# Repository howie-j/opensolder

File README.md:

# OpenSolder
  
Fully open source JBC T245-compatible soldering station and iron holder

## Introduction
When my cheap T12 clone soldering station went up in smoke, i started looking into either buying a JBC CDB, or building a proper soldering station. The internet is already crowded with DIY JBC compatible stations, but most are poorly documented, or does not have the quality-of-life features that the original have.

The [unisolder project](https://github.com/sparkybg/UniSolder-5.2) is absolutely impressive, but waaay to complex and "universal" for my needs. [Marco Reps](https://youtu.be/GYIiOkr6x9o) built a cool C470 station, and i liked the simplicity of that.

## Goals:
- _T12 clone like_ form factor station that does not take up valuable bench space
- JBC T245 tip compatibility, with similar performance to the original station
- QoL features that the CDB station have, like auto standby, tip remover, holder, tip cleaner ect.
- Simple design using cheap off-the-shelf parts
- A compact handle stand with these features:
	- Detection when the handle is in the tool holder (auto standby)
	- Detection when you're about to swap tips (cut power)
	- Integrated tip remover, tip storage, tip cleaner and a soldering wire spool holder
	- Simple to build

## Design Specifications
- 24V toroidal transformer
- Zero Crossing AC switching
- OLED display and rotary encoder for adjusting temperature
- Compact and low profile design
- Super fast heatup time
- Hardware should be mostly 3D printable, and easy to build using regular tools

## Station
  
The station is built in a Hammond enclosure, with a center mounted transformer. The PCB is mounted to the custom front panel, and all 230VAC connections is in the rear of the chassis.
There is two connectors on the rear panel, one for connecting to the stand, and an optional ST-link connector for firmware upgrades.

## Stand
  
The stand consists of 3D-printed parts, a genuine JBC tool holder, a tip remover made from aluminium angle and some hardware. 

## Schematic

## PCB

The PCB is fairly low density, uses 0805 SMD components and is fully hand solderable with a microscope.

[Check out the awesome interactive BOM!](http://htmlpreview.github.io/?https://github.com/howie-j/OpenSolder/blob/main/Electronics/BOM/Interactive_BOM.html)

## Firmware
Coming soon... :)

## Links and Sources

[The unisolder project](https://github.com/sparkybg/UniSolder-5.2)  
[Marco Reps](https://youtu.be/GYIiOkr6x9o)  
[foldvarid93's JBC Soldering Station](https://github.com/foldvarid93/JBC_SolderingStation)  
[johnmx's eevblog thread](https://eevblog.com/forum/testgear/jbc-soldering-station-cd-2bc-complete-schematic-analysis/)

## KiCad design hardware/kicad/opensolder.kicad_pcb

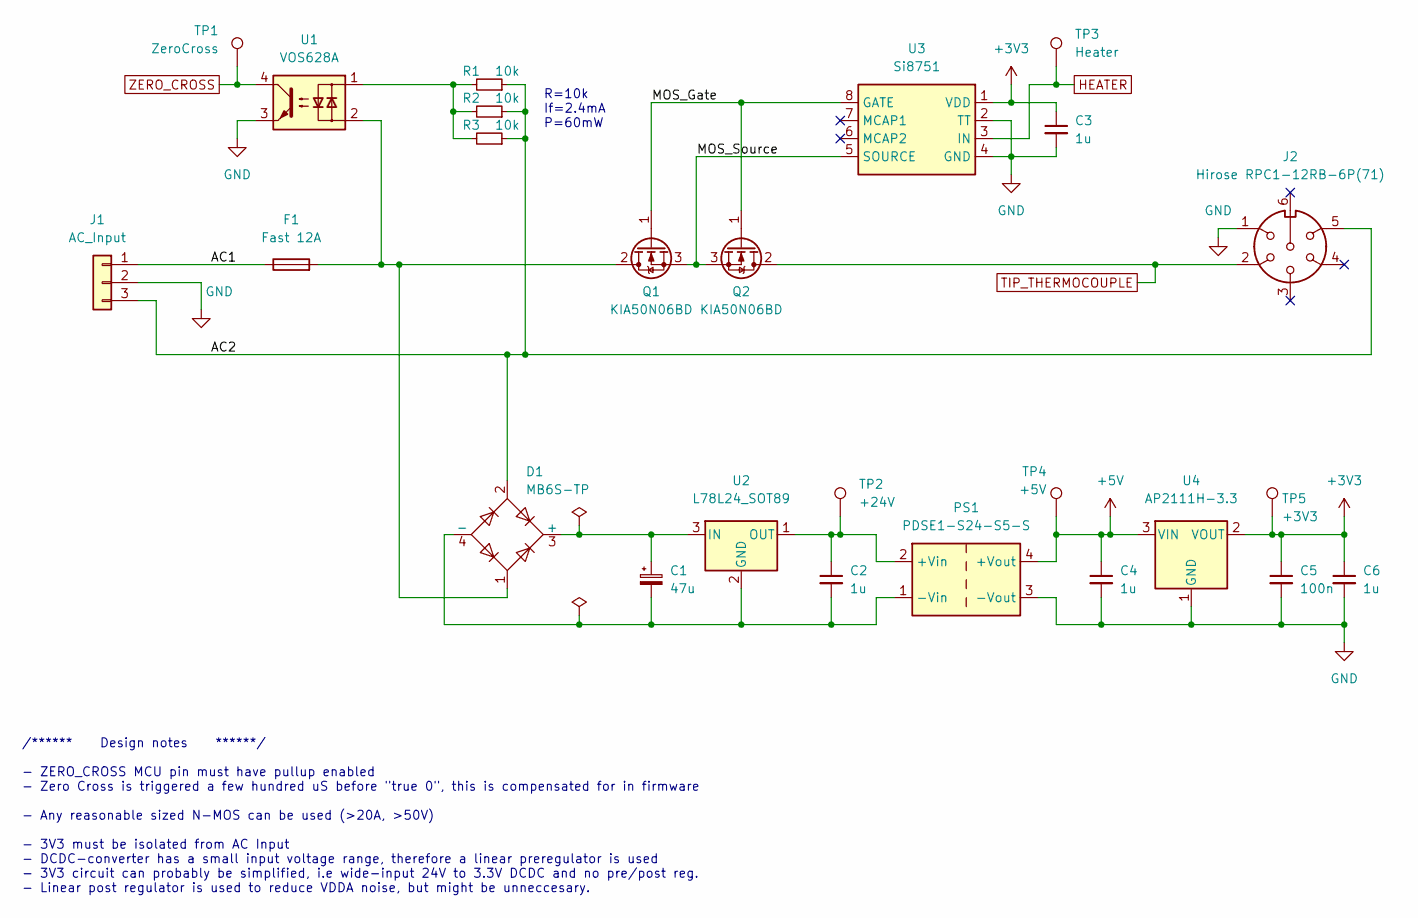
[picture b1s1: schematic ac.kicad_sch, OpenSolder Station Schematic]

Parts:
C1: 47u; CP_Radial_D8.0mm_P3.50mm
C2, C3, C4, C6: 1u; C_1210_3225Metric
C5: 100n; C_0805_2012Metric
D1: MB6S-TP; TO-269AA
F1: Fast 12A; Fuseholder_Cylinder-5x20mm_Schurter_0031_8201_Horizontal_Op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
J1: AC_Input; PhoenixContact_MSTBVA_2,5_3-G_1x03_P5.00mm_Vertical
J2: Hirose RPC1-12RB-6P(71); Hirose_RPC1
PS1: PDSE1-S24-S5-S; PDSE1_DCDC
Q1, Q2: KIA50N06BD; TO-252-2
R1, R2, R3: 10k; R_0805_2012Metric
TP1: ZeroCross; TestPoint_Pad_D1.0mm
TP2: +24V; TestPoint_Pad_D1.0mm
TP3: Heater; TestPoint_Pad_D1.0mm
TP4: +5V; TestPoint_Pad_D1.0mm
TP5: +3V3; TestPoint_Pad_D1.0mm
U1: VOS628A; SOP-4_4.4x2.6mm_P1.27mm
U2: L78L24_SOT89; SOT-89-3
U3: Si8751; SOIC-8_3.9x4.9mm_P1.27mm
U4: AP2111H-3.3; SOT-223

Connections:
+3V3: C3.1, C5.1, C6.1, TP5.1, U3.1 (VDD), U4.2 (VOUT); also elsewhere on the board
+5V: C4.1, PS1.4 (+Vout), TP4.1, U4.3 (VIN)
/AC/AC1: F1.1, J1.1
/AC/AC2: D1.2, J1.3, J2.5, R1.1, R2.1, R3.1
/AC/MOS_Gate: Q1.1 (G), Q2.1 (G), U3.8 (GATE)
/AC/MOS_Source: Q1.3 (S), Q2.3 (S), U3.5 (SOURCE)
GND: C3.2, C4.2, C5.2, C6.2, J1.2, J2.1, PS1.3 (-Vout), U1.3, U3.2 (TT), U3.4 (GND), U4.1 (GND); also elsewhere on the board
HEATER: TP3.1, U3.3 (IN); also elsewhere on the board
unnamed: C1.1, D1.3 (+), U2.3 (IN)
unnamed: C1.2, C2.2, D1.4 (-), PS1.1 (-Vin), U2.2 (GND)
unnamed: C2.1, PS1.2 (+Vin), TP2.1, U2.1 (OUT)
unnamed: D1.1, F1.2, Q1.2 (D), U1.2
unnamed: R1.2, R2.2, R3.2, U1.1
TIP_THERMOCOUPLE: J2.2, Q2.2 (D); also elsewhere on the board
ZERO_CROSS: TP1.1, U1.4; also elsewhere on the board

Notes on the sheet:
R=10k If=2.4mA P=60mW
/****** Design notes ******/ - ZERO_CROSS MCU pin must have pullup enabled - Zero Cross is triggered a few hundred uS before "true 0", this is compensated for in firmware - Any reasonable sized N-MOS can be used (>20A, >50V) - 3V3 must be isolated from AC Input - DCDC-converter has a small input vo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

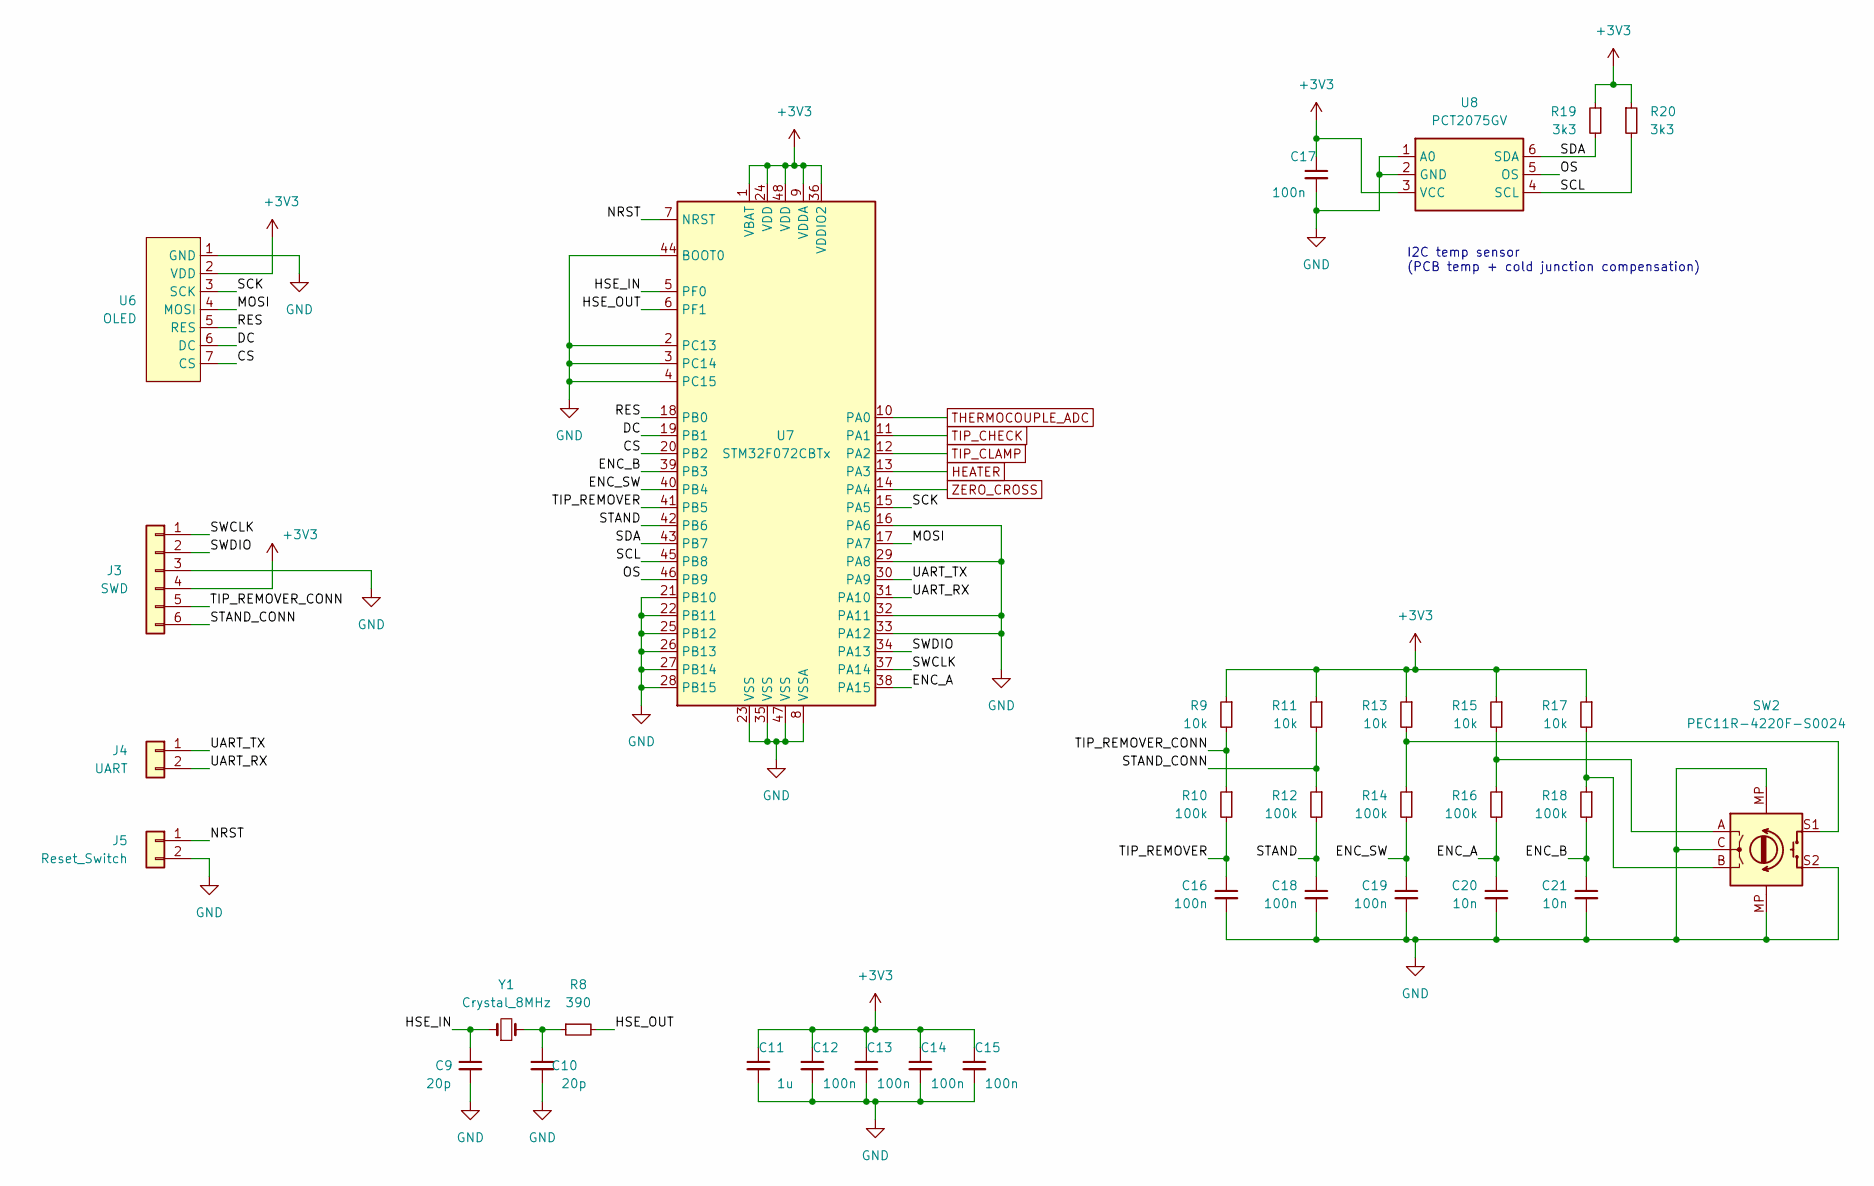
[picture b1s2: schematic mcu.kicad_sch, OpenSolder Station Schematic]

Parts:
C9, C10: 20p; C_0805_2012Metric
C11: 1u; C_1210_3225Metric
C12, C13, C14, C15, C16, C17, C18, C19: 100n; C_0805_2012Metric
C20, C21: 10n; C_0805_2012Metric
J3: SWD; IDC-Header_2x03_P2.54mm_Vertical
J4: UART; PinSocket_1x02_P2.54mm_Vertical
J5: Reset_Switch; PinSocket_1x02_P2.54mm_Vertical
R8: 390; R_0805_2012Metric
R9, R11, R13, R15, R17: 10k; R_0805_2012Metric
R10, R12, R14, R16, R18: 100k; R_0805_2012Metric
R19, R20: 3k3; R_0805_2012Metric
SW2: PEC11R-4220F-S0024; RotaryEncoder_PEC11R_PEC12R
U6: OLED; OLED_SSD1306_SPI_1.54
U7: STM32F072CBTx; LQFP-48_7x7mm_P0.5mm
U8: PCT2075GV; TSOP-6_1.65x3.05mm_P0.95mm
Y1: Crystal_8MHz; Crystal_SMD_HC49-SD

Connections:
+3V3: C11.1, C12.1, C13.1, C14.1, C15.1, C17.1, J3.4, R9.1, R11.1, R13.1, R15.1, R17.1, R19.1, R20.1, U6.2 (VDD), U7.1 (VBAT), U7.9 (VDDA), U7.24 (VDD), U7.36 (VDDIO2), U7.48 (VDD), U8.3 (VCC); also elsewhere on the board
/MCU/CS: U6.7 (CS), U7.20 (PB2)
/MCU/DC: U6.6 (DC), U7.19 (PB1)
/MCU/ENC_A: C20.1, R16.2, U7.38 (PA15)
/MCU/ENC_B: C21.1, R18.2, U7.39 (PB3)
/MCU/ENC_SW: C19.1, R14.2, U7.40 (PB4)
/MCU/HSE_IN: C9.1, U7.5 (PF0), Y1.1
/MCU/HSE_OUT: R8.2, U7.6 (PF1)
/MCU/MOSI: U6.4 (MOSI), U7.17 (PA7)
/MCU/NRST: J5.1, U7.7 (NRST)
/MCU/OS: U7.46 (PB9), U8.5 (OS)
/MCU/RES: U6.5 (RES), U7.18 (PB0)
/MCU/SCK: U6.3 (SCK), U7.15 (PA5)
/MCU/SCL: R20.2, U7.45 (PB8), U8.4 (SCL)
/MCU/SDA: R19.2, U7.43 (PB7), U8.6 (SDA)
/MCU/STAND: C18.1, R12.2, U7.42 (PB6)
/MCU/STAND_CONN: J3.6, R11.2, R12.1
/MCU/SWCLK: J3.1, U7.37 (PA14)
/MCU/SWDIO: J3.2, U7.34 (PA13)
/MCU/TIP_REMOVER: C16.1, R10.2, U7.41 (PB5)
/MCU/TIP_REMOVER_CONN: J3.5, R9.2, R10.1
/MCU/UART_RX: J4.2, U7.31 (PA10)
/MCU/UART_TX: J4.1, U7.30 (PA9)
GND: C9.2, C10.2, C11.2, C12.2, C13.2, C14.2, C15.2, C16.2, C17.2, C18.2, C19.2, C20.2, C21.2, J3.3, J5.2, SW2.C, SW2.MP, SW2.S2, U6.1 (GND), U7.2 (PC13), U7.3 (PC14), U7.4 (PC15), U7.8 (VSSA), U7.16 (PA6), U7.21 (PB10), U7.22 (PB11), U7.23 (VSS), U7.25 (PB12), U7.26 (PB13), U7.27 (PB14), U7.28 (PB15), U7.29 (PA8), U7.32 (PA11), U7.33 (PA12), U7.35 (VSS), U7.44 (BOOT0), U7.47 (VSS), U8.1 (A0), U8.2 (GND); also elsewhere on the board
HEATER: U7.13 (PA3); also elsewhere on the board
unnamed: C10.1, R8.1, Y1.2
unnamed: R13.2, R14.1, SW2.S1
unnamed: R15.2, R16.1, SW2.A
unnamed: R17.2, R18.1, SW2.B
THERMOCOUPLE_ADC: U7.10 (PA0); also elsewhere on the board
TIP_CHECK: U7.11 (PA1); also elsewhere on the board
TIP_CLAMP: U7.12 (PA2); also elsewhere on the board
ZERO_CROSS: U7.14 (PA4); also elsewhere on the board

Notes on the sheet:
I2C temp sensor (PCB temp + cold junction compensation)

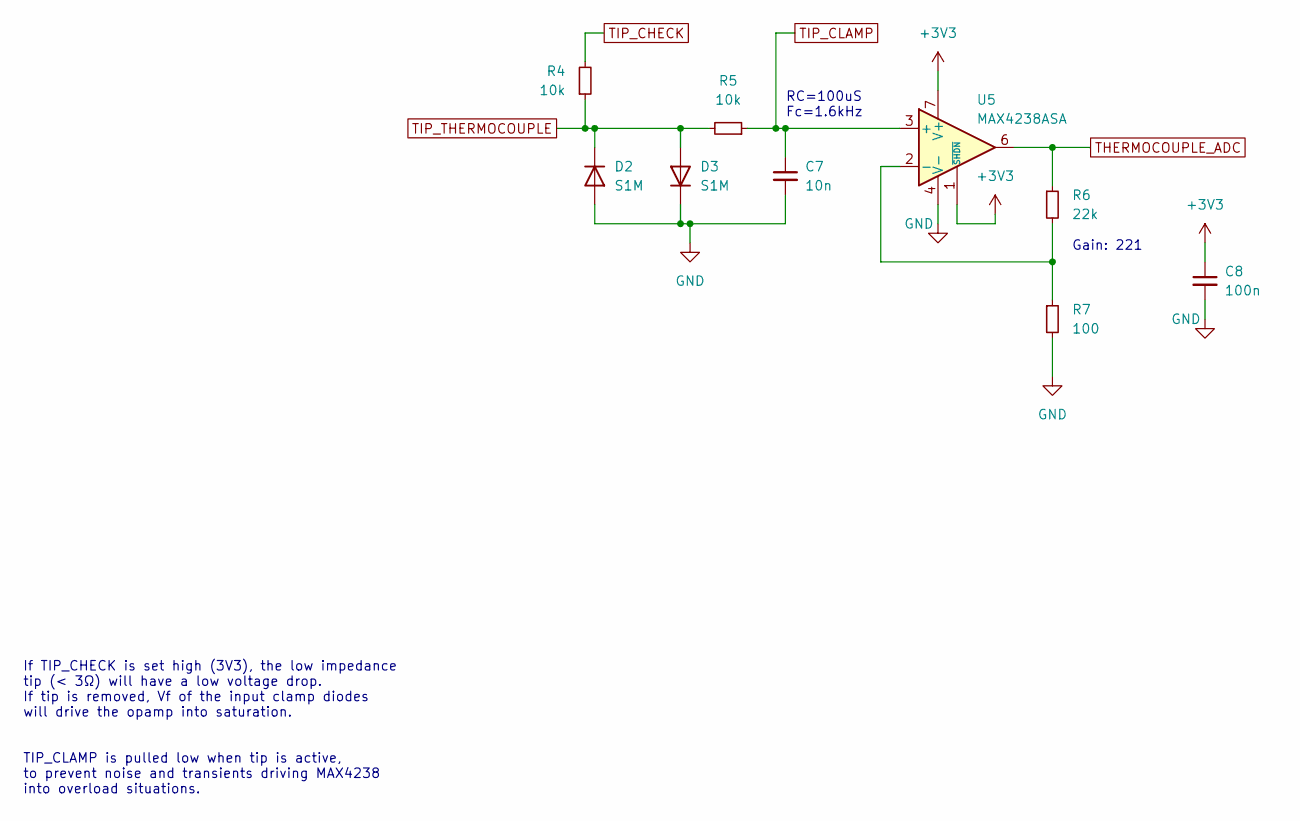
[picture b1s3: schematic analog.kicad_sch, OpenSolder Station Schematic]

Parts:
C7: 10n; C_0805_2012Metric
C8: 100n; C_0805_2012Metric
D2, D3: S1M; D_SMA
R4, R5: 10k; R_0805_2012Metric
R6: 22k; R_0805_2012Metric
R7: 100; R_0805_2012Metric
U5: MAX4238ASA; SOIC-8_3.9x4.9mm_P1.27mm

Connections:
+3V3: C8.1, U5.1 (~SHDN), U5.7 (V+); also elsewhere on the board
GND: C7.2, C8.2, D2.2 (A), D3.1 (K), R7.2, U5.4 (V-); also elsewhere on the board
unnamed: R6.2, R7.1, U5.2 (-)
THERMOCOUPLE_ADC: R6.1, U5.6; also elsewhere on the board
TIP_CHECK: R4.2; also elsewhere on the board
TIP_CLAMP: C7.1, R5.1, U5.3 (+); also elsewhere on the board
TIP_THERMOCOUPLE: D2.1 (K), D3.2 (A), R4.1, R5.2; also elsewhere on the board

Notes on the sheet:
Gain: 221
RC=100uS Fc=1.6kHz
If TIP_CHECK is set high (3V3), the low impedance tip (< 3Ω) will have a low voltage drop. If tip is removed, Vf of the input clamp diodes will drive the opamp into saturation. TIP_CLAMP is pulled low when tip is active, to prevent noise and transients driving MAX4238 into overload situations.

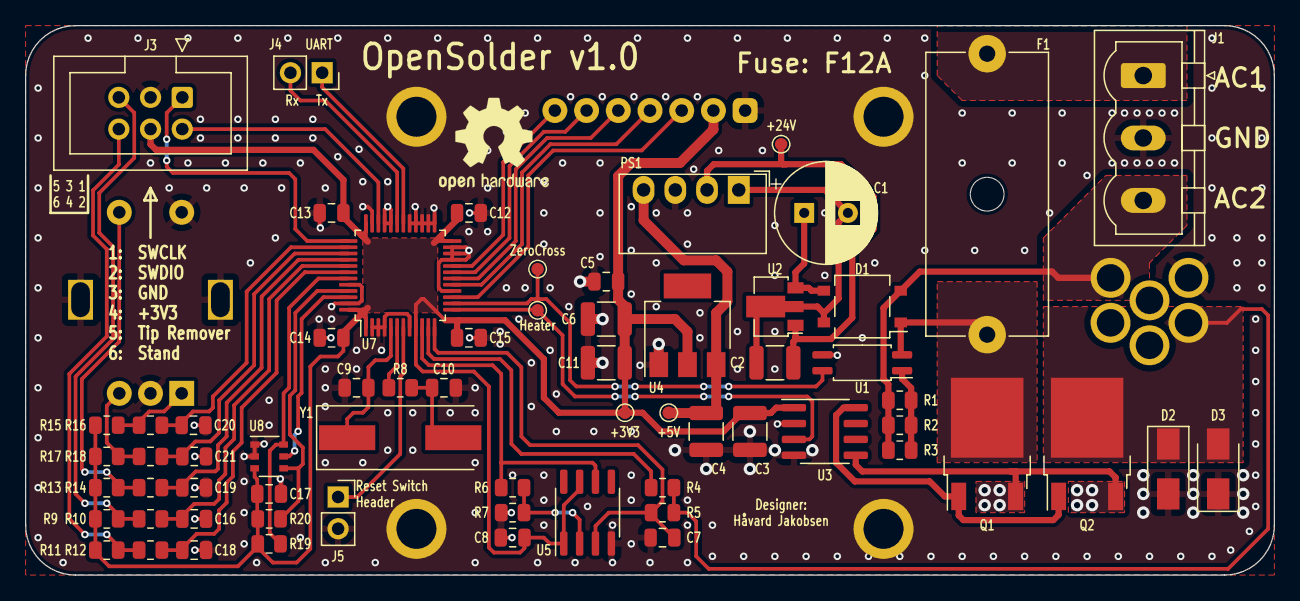
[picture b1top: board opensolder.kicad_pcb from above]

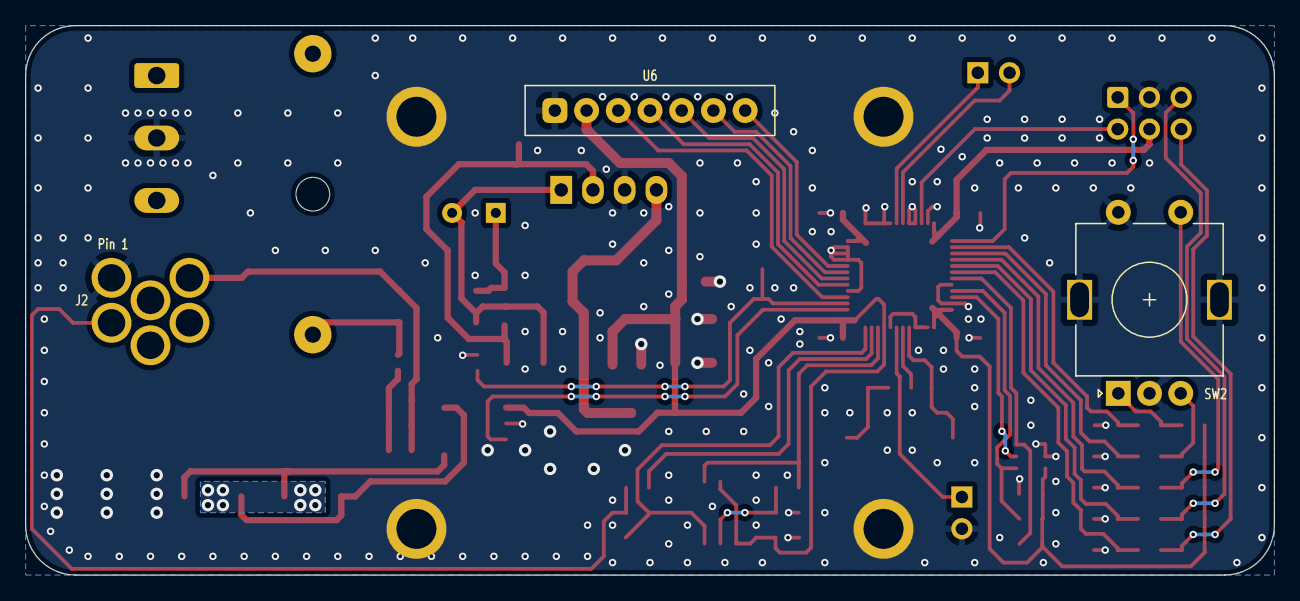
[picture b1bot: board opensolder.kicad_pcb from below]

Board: 2 copper layers, 100.0 x 44.0 mm, 68 parts (3 on the bottom side), 45 nets.

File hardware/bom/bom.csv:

Item,Qty,Reference(s),Value,LibPart,Footprint,Datasheet
1,1,C1,47u,Device:C_Polarized_Small,Capacitor_THT:CP_Radial_D8.0mm_P3.50mm,~
2,5,"C2, C3, C4, C6, C11",1u,Device:C_Small,Capacitor_SMD:C_1210_3225Metric,~
3,10,"C5, C8, C12, C13, C14, C15, C16, C17, C18, C19",100n,Device:C_Small,Capacitor_SMD:C_0805_2012Metric,~
4,3,"C7, C20, C21",10n,Device:C_Small,Capacitor_SMD:C_0805_2012Metric,~
5,2,"C9, C10",20p,Device:C_Small,Capacitor_SMD:C_0805_2012Metric,~
6,1,D1,MB6S-TP,0_Howie:MB6S-TP,Package_TO_SOT_SMD:TO-269AA,
7,2,"D2, D3",S1M,0_Howie:S1M,Diode_SMD:D_SMA,
8,1,F1,Fast 12A,Device:Fuse,Fuse:Fuseholder_Cylinder-5x20mm_Schurter_0031_8201_Horizontal_Open,~
9,1,J1,AC_Input,Connector_Generic:Conn_01x03,"Connector_Phoenix_MSTB:PhoenixContact_MSTBVA_2,5_3-G_1x03_P5.00mm_Vertical",~
10,1,J2,Hirose RPC1-12RB-6P(71),0_Howie:Hirose RPC1-12RB-6P(71),0_Howie:Hirose_RPC1,
11,1,J3,SWD,Connector_Generic:Conn_01x06,Connector_IDC:IDC-Header_2x03_P2.54mm_Vertical,~
12,1,J4,UART,Connector_Generic:Conn_01x02,Connector_PinSocket_2.54mm:PinSocket_1x02_P2.54mm_Vertical,~
13,1,J5,Reset_Switch,Connector_Generic:Conn_01x02,Connector_PinSocket_2.54mm:PinSocket_1x02_P2.54mm_Vertical,~
14,1,PS1,PDSE1-S24-S5-S,0_Howie:PDSE1-S24-S5-S,0_Howie:PDSE1_DCDC,
15,2,"Q1, Q2",KIA50N06BD,0_Howie:KIA50N06BD,Package_TO_SOT_SMD:TO-252-2,
16,10,"R1, R2, R3, R4, R5, R9, R11, R13, R15, R17",10k,Device:R_Small,Resistor_SMD:R_0805_2012Metric,~
17,1,R6,22k,Device:R_Small,Resistor_SMD:R_0805_2012Metric,~
18,1,R7,100,Device:R_Small,Resistor_SMD:R_0805_2012Metric,~
19,1,R8,390,Device:R_Small,Resistor_SMD:R_0805_2012Metric,~
20,5,"R10, R12, R14, R16, R18",100k,Device:R_Small,Resistor_SMD:R_0805_2012Metric,~
21,2,"R19, R20",3k3,Device:R_Small,Resistor_SMD:R_0805_2012Metric,~
22,1,SW2,PEC11R-4220F-S0024,0_Howie:PEC11R-RotEnc,0_Howie:RotaryEncoder_PEC11R_PEC12R,~
23,1,TP1,ZeroCross,0_Howie:TestPoint_D1_Pad,TestPoint:TestPoint_Pad_D1.0mm,~
24,1,TP2,+24V,0_Howie:TestPoint_D1_Pad,TestPoint:TestPoint_Pad_D1.0mm,~
25,1,TP3,Heater,0_Howie:TestPoint_D1_Pad,TestPoint:TestPoint_Pad_D1.0mm,~
26,1,TP4,+5V,0_Howie:TestPoint_D1_Pad,TestPoint:TestPoint_Pad_D1.0mm,~
27,1,TP5,+3V3,0_Howie:TestPoint_D1_Pad,TestPoint:TestPoint_Pad_D1.0mm,~
28,1,U1,VOS628A,0_Howie:VOS628A,Package_SO:SOP-4_4.4x2.6mm_P1.27mm,
29,1,U2,L78L24_SOT89,Regulator_Linear:L78L24_SOT89,Package_TO_SOT_SMD:SOT-89-3,http://www.st.com/content/ccc/resource/technical/document/da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
30,1,U3,Si8751,0_Howie:Si8751,Package_SO:SOIC-8_3.9x4.9mm_P1.27mm,
31,1,U4,AP2111H-3.3,0_Howie:AP2111H-3.3,Package_TO_SOT_SMD:SOT-223,
32,1,U5,MAX4238ASA,Amplifier_Operational:MAX4238ASA,Package_SO:SOIC-8_3.9x4.9mm_P1.27mm,http://datasheets.maximintegrated.com/en/ds/MAX4238-MAX4239.pdf
33,1,U6,OLED,0_Howie:OLED_SSD1306_SPI_1.54,0_Howie:OLED_SSD1306_SPI_1.54,
34,1,U7,STM32F072CBTx,MCU_ST_STM32F0:STM32F072CBTx,Package_QFP:LQFP-48_7x7mm_P0.5mm,http://www.st.com/st-web-ui/static/active/en/resource/techni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
35,1,U8,PCT2075GV,0_Howie:PCT2075GV,Package_SO:TSOP-6_1.65x3.05mm_P0.95mm,https://www.nxp.com/docs/en/data-sheet/PCT2075.pdf
36,1,Y1,Crystal_8MHz,0_Howie:Crystal_8MHz,Crystal:Crystal_SMD_HC49-SD,~

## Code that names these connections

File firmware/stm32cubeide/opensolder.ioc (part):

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Mcu.Name=STM32F072C(8-B)Tx
Mcu.Package=LQFP48
Mcu.UserName=STM32F072CBTx
PA0.GPIOParameters=GPIO_Label
PA0.GPIO_Label=THERMOCOUPLE_ADC
PA0.Mode=IN0
PA0.Signal=ADC_IN0
PA1.GPIOParameters=GPIO_Label
PA1.GPIO_Label=TIP_CHECK
PA1.Signal=GPIO_Input
PA13.Mode=Serial_Wire
PA13.Signal=SYS_SWDIO
PA14.Mode=Serial_Wire
PA14.Signal=SYS_SWCLK
PA15.GPIOParameters=GPIO_Label
PA15.GPIO_Label=ENC_A
PA15.Signal=S_TIM2_CH1_ETR
PA2.GPIOParameters=GPIO_Label
PA2.GPIO_Label=TIP_CLAMP
PA2.Signal=GPIO_Input
PA3.GPIOParameters=GPIO_Label
PA3.GPIO_Label=HEATER
PA3.Signal=GPIO_Output
PA4.GPIOParameters=GPIO_PuPd,GPIO_Label
PA4.GPIO_Label=ZERO_CROSS
PA4.GPIO_PuPd=GPIO_PULLUP
PA4.Signal=GPXTI4
PA5.Mode=Simplex_Bidirectional_Master
PA5.Signal=SPI1_SCK
PA7.Mode=Simplex_Bidirectional_Master
PA7.Signal=SPI1_MOSI
PB0.GPIOParameters=GPIO_Label
PB0.GPIO_Label=RES
PB0.Signal=GPIO_Output
PB1.GPIOParameters=GPIO_Label
PB1.GPIO_Label=DC
PB1.Signal=GPIO_Output
PB2.GPIOParameters=GPIO_Label
PB2.GPIO_Label=CS
PB2.Signal=GPIO_Output
PB3.GPIOParameters=GPIO_Label
PB3.GPIO_Label=ENC_B
PB3.Signal=S_TIM2_CH2
PB4.GPIOParameters=GPIO_Label
PB4.GPIO_Label=ENC_SW
PB4.Signal=GPIO_Input
PB5.GPIOParameters=GPIO_PuPd,GPIO_Label
PB5.GPIO_Label=TIP_REMOVER
PB5.GPIO_PuPd=GPIO_NOPULL
PB5.Signal=GPIO_Input
PB6.GPIOParameters=GPIO_PuPd,GPIO_Label
PB6.GPIO_Label=STAND
PB6.GPIO_PuPd=GPIO_NOPULL
PB6.Signal=GPIO_Input
PB7.Mode=I2C
PB7.Signal=I2C1_SDA
PB8.Mode=I2C
PB8.Signal=I2C1_SCL
PB9.GPIOParameters=GPIO_PuPd,GPIO_Label
PB9.GPIO_Label=OS
PB9.GPIO_PuPd=GPIO_PULLUP
PB9.Signal=GPIO_Input
PF0-OSC_IN.Mode=HSE-External-Oscillator
PF0-OSC_IN.Signal=RCC_OSC_IN
PF1-OSC_OUT.Mode=HSE-External-Oscillator
PF1-OSC_OUT.Signal=RCC_OSC_OUT
RCC.SYSCLKFreq_VALUE=48000000
RCC.SYSCLKSource=RCC_SYSCLKSOURCE_PLLCLK
board=custom

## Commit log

2022-05-10 Initial "Hardware" commit
2022-05-10 Initial "Electronics" commit
2022-05-10 Initial "Firmware" commit
2022-05-10 Readme preview
2022-05-10 Readme preview 2
2022-05-10 Readme preview 3
2022-05-10 Readme preview 4
2022-05-10 Readme preview 5
2022-05-10 Readme preview 6
2022-05-10 Readme preview 7
2022-05-10 Readme preview 8
2022-05-10 Readme preview 9
2022-05-10 Readme preview 10
2023-04-08 firmware + batch file renaming MixedCase to lower_case
2023-04-08 Update readme.md
    repaired links
2023-04-08 short fw description
2023-04-08 Renamed stm32cubeide -> opensolder to match project name
2023-04-08 Fix constants default value
2023-04-08 Fixed tip_change display bug
2023-07-10 Update default values

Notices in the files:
hardware/kicad/ac.kicad_sch:
Licence: GPL-3.0
